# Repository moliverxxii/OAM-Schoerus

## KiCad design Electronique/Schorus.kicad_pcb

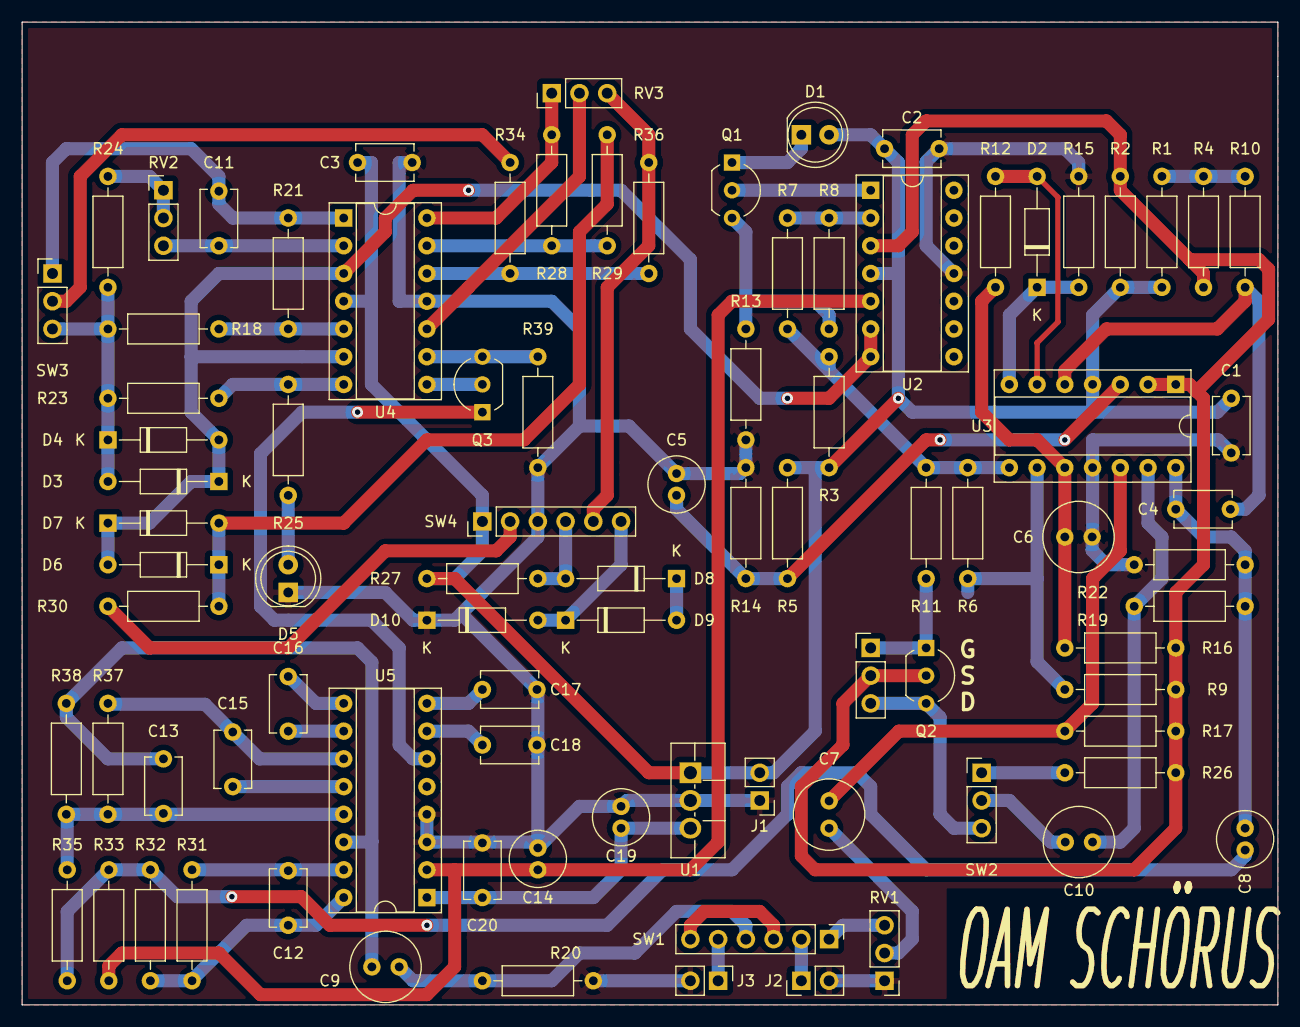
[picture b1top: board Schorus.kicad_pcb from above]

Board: 2 copper layers, 115.0 x 90.0 mm, 87 parts (0 on the bottom side), 63 nets.

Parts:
C1, C2, C3, C4, C11, C17, C18, C20: 100nF; C_Disc_D5.1mm_W3.2mm_P5.00mm
C5, C8: 10µF; C_Radial_D5.0mm_H11.0mm_P2.00mm
C6, C7, C9, C10: 1µF; C_Radial_D6.3mm_H11.0mm_P2.50mm
C12, C13: 680pF; C_Disc_D5.1mm_W3.2mm_P5.00mm
C14: 47µF; C_Radial_D5.0mm_H11.0mm_P2.00mm
C15, C16: 10nF; C_Disc_D5.1mm_W3.2mm_P5.00mm
C19: 100µF; C_Radial_D5.0mm_H11.0mm_P2.00mm
D1, D5: LED; LED_D5.0mm
D2, D3, D4, D6, D7, D8, D9, D10: 1N4148; D_DO-35_SOD27_P10.16mm_Horizontal
J1: Coaxial connector 2.1mm; PinHeader_1x02_P2.54mm_Vertical
J2, J3: 1/4 inch jack; PinHeader_1x02_P2.54mm_Vertical_Jack
Q1, Q3: BC548; TO-92_Inline_Wide
Q2: BF245C; TO-92_Inline_Wide
R1, R6, R7, R8, R18, R21, R28, R29, R33, R34, R36: 1MΩ; R_Axial_DIN0207_L6.3mm_D2.5mm_P10.16mm_Horizontal
R2, R19, R23, R25, R27: 4.7kΩ; R_Axial_DIN0207_L6.3mm_D2.5mm_P10.16mm_Horizontal
R3, R10, R11, R17, R20: 100kΩ; R_Axial_DIN0207_L6.3mm_D2.5mm_P10.16mm_Horizontal
R4, R12: 470Ω; R_Axial_DIN0207_L6.3mm_D2.5mm_P10.16mm_Horizontal
R5, R14: 47kΩ; R_Axial_DIN0207_L6.3mm_D2.5mm_P10.16mm_Horizontal
R9: 33kΩ; R_Axial_DIN0207_L6.3mm_D2.5mm_P10.16mm_Horizontal
R13, R24, R31, R37: 10kΩ; R_Axial_DIN0207_L6.3mm_D2.5mm_P10.16mm_Horizontal
R15: 2.2kΩ; R_Axial_DIN0207_L6.3mm_D2.5mm_P10.16mm_Horizontal
R16: 470kΩ; R_Axial_DIN0207_L6.3mm_D2.5mm_P10.16mm_Horizontal
R22: 3.3kΩ; R_Axial_DIN0207_L6.3mm_D2.5mm_P10.16mm_Horizontal
R26, R30, R39: 1kΩ; R_Axial_DIN0207_L6.3mm_D2.5mm_P10.16mm_Horizontal
R32, R35: 15kΩ; R_Axial_DIN0207_L6.3mm_D2.5mm_P10.16mm_Horizontal
R38: 10k; R_Axial_DIN0207_L6.3mm_D2.5mm_P10.16mm_Horizontal
RV1, RV2: A500kΩ; PinHeader_1x03_P2.54mm_Vertical
RV3: 500kΩ; PinHeader_1x03_P2.54mm_Vertical
SW1: 3PDT; PinHeader_1x06_P2.54mm_Vertical
SW2, SW3: SPDT; PinHeader_1x03_P2.54mm_Vertical
SW4: DPDT; PinHeader_1x06_P2.54mm_Vertical
U1: LM7805; TO-220F-3_Vertical
U2, U3, U4: LM324N; DIP-14_W7.62mm_Socket
U5: PT2399; DIP-16_W7.62mm_Socket

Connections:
+5V: C19.1, C20.1, U1.3, U5.1
+9V: C1.1, C2.1, C3.1, D1.2, J1.2, R1.2, R2.2, R3.2, R5.2, R27.2, SW4.1, U1.1, U2.4, U3.4, U4.4
/COMP_CV: Q2.1, R11.2
/COMP_OUT: C4.1, C8.1, R19.2, R22.2, U3.14
/REF: D3.1, D4.2, D6.2, D7.1, U2.6, U2.7, U4.3, U4.6
GND: C1.2, C2.2, C3.2, C5.2, C6.2, C14.2, C17.2, C18.2, C19.2, C20.2, D5.1, D10.1, J1.1, J2.S, J3.S, R13.1, R14.1, R15.2, R20.1, R22.1, R39.1, RV1.1, SW4.3, U1.2, U2.11, U3.11, U4.11, U5.3, U5.4
unnamed: C4.2, R10.1, U3.5
unnamed: C5.1, R5.1, R14.2, U3.3
unnamed: C6.1, R12.1, R16.2, U3.10
unnamed: C7.1, RV1.2
unnamed: C7.2, R17.2, U3.12
unnamed: C8.2, R32.2, R33.2, R35.1
unnamed: C9.1, R20.2, SW1.4
unnamed: C10.1, R19.1, U3.13
unnamed: C10.2, SW2.2
unnamed: C11.1, RV2.3, U4.2
unnamed: C11.2, R21.2, SW3.1, U4.1
unnamed: C12.1, R31.2, R32.1, U5.16
unnamed: C12.2, R31.1, U5.15
unnamed: C9.2, C13.1, R38.2, U5.14
unnamed: C13.2, R35.2, R37.2, R38.1, U5.13
unnamed: C14.1, R33.1, U2.5, U5.2
unnamed: C15.1, U5.12
unnamed: C15.2, R37.1, U5.11
unnamed: C16.1, U5.10
unnamed: C16.2, U5.9
unnamed: C17.1, U5.8
unnamed: C18.1, U5.7
unnamed: D1.1, Q1.1
unnamed: D2.1, R15.1, U3.7
unnamed: D2.2, R12.2, U3.6
unnamed: D3.2, D4.1, R18.1, R23.1, R24.2, SW3.3
unnamed: D5.2, R25.1
unnamed: D6.1, D7.2, R29.1, R30.2
unnamed: D8.1, D9.2
unnamed: D8.2, R27.1, SW4.4
unnamed: D9.1, D10.2, SW4.6
unnamed: J2.T, SW1.2
unnamed: J3.T, SW1.5
unnamed: Q1.2, U2.1
unnamed: Q1.3, R8.1, R13.2
unnamed: Q2.3, SW2.3
unnamed: Q3.1, U5.6
unnamed: Q3.2, U4.8
unnamed: Q3.3, R39.2, U4.9
unnamed: R1.1, R4.2, R10.2
unnamed: R6.2, R9.1, U3.9
unnamed: R7.1, R8.2, U2.2
unnamed: R3.1, R6.1, R7.2, R11.1, U3.8
unnamed: R18.2, R21.1, U4.5
unnamed: R23.2, R25.2, U4.7
unnamed: R24.1, RV2.1, RV2.2
unnamed: R26.2, SW2.1
unnamed: R28.1, R29.2, U4.13
unnamed: R28.2, RV3.1, U4.14
unnamed: R30.1, SW4.2
unnamed: R34.1, SW3.2
unnamed: R34.2, R36.2, U4.12
unnamed: R36.1, RV3.3, SW4.5
unnamed: RV1.3, SW1.1
unnamed: RV3.2, U4.10
unnamed: SW1.3, SW1.6
VCOM: Q2.2, R2.1, R4.1, R9.2, R16.1, R17.1, R26.1, U2.3, U3.1, U3.2

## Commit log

2023-06-26 Schéma initial.
2023-07-02 Noms de fichier.
2023-07-24 Placement des empreintes.
2023-07-24 Circuit imprimé en attente d'être imprimé par un professionnel.
2023-07-24 Rendu du schéma en PDF
2023-07-24 Faute de référence commentaires interrupteurs.
2023-07-25 Logo sur le circuit imprimé
2023-07-26 Rev 0
2025-04-30 commentaires de l'erreur rev0.
